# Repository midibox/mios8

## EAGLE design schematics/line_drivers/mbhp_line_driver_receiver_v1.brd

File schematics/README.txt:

Schematics can be viewed and edited with XCircuit
-> http://opencircuitdesign.com/xcircuit/

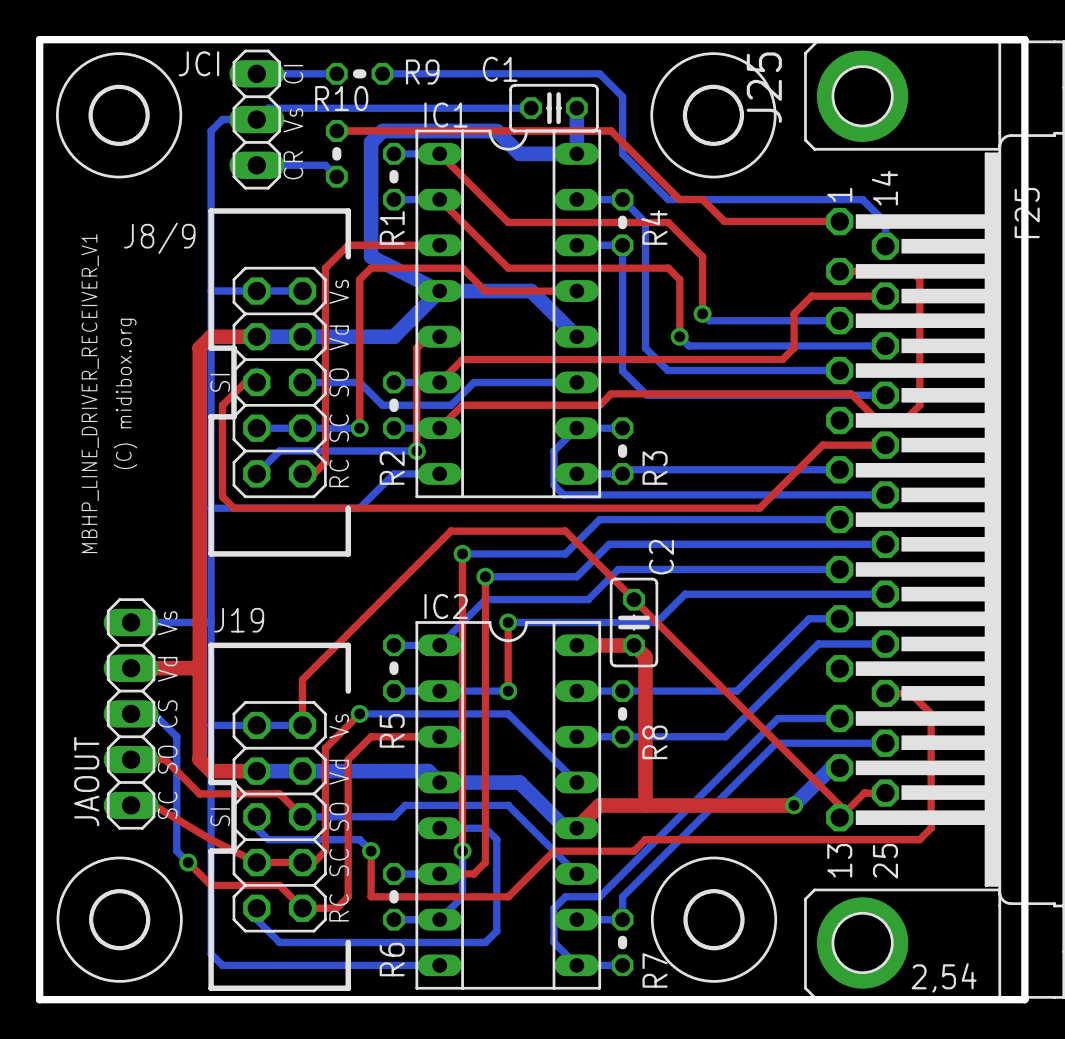
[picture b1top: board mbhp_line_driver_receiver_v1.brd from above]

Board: 2 copper layers, 54.7 x 53.3 mm, 23 parts (0 on the bottom side), 32 nets.

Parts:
C1, C2: 100n; C025-025X050
E$1, E$2, E$4, E$7: 3,0
IC1, IC2: MC3486; SOCKET-16
J8/9, J19: 2X05
J25: F25HP
JAOUT: 1X05
JCI: 1X03
R1, R2, R3, R4, R5, R6, R7, R8, R9, R10: 100; 0204V

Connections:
5V: C1.2, C2.2, IC1.4, IC1.12, IC1.16, IC2.4, IC2.12, IC2.16, J8/9.3, J8/9.4, J19.3, J19.4, J25.12, JAOUT.4
GND: C1.1, C2.1, IC1.8, IC2.8, J8/9.1, J8/9.2, J19.1, J19.2, J25.13, J25.25, JAOUT.5, JCI.2
S$1: IC2.11, J19.6, JAOUT.2
S$2: J19.5, J25.23
S$3: IC2.3, J19.10, JAOUT.3
S$4: IC2.13, J19.7, J19.8, JAOUT.1
S$5: IC2.5, J19.9
S$6: IC1.3, J8/9.10
S$7: IC1.5, J8/9.9
S$8: IC1.11, J8/9.6
S$9: IC1.13, J8/9.7, J8/9.8
S$10: IC1.15, J25.4, R4.1
S$11: IC1.14, J25.17, R4.2
S$12: IC1.10, J25.19, R3.1
S$13: IC1.9, J25.6, R3.2
S$14: IC2.15, J25.9, R8.1
S$15: IC2.14, J25.22, R8.2
S$16: IC2.10, J25.24, R7.1
S$17: IC2.9, J25.11, R7.2
S$18: IC2.2, J25.21, R5.2
S$19: IC2.1, J25.8, R5.1
S$21: IC2.6, J25.20, R6.1
S$22: IC2.7, J25.7, R6.2
S$24: IC1.7, J25.2, R2.2
S$25: IC1.6, J25.15, R2.1
S$26: IC1.2, J25.16, R1.2
S$27: IC1.1, J25.3, R1.1
S$28: JCI.1, R10.2
S$29: JCI.3, R9.2
S$30: J25.14, R9.1
S$31: J25.1, R10.1
SI1: J8/9.5, J25.18

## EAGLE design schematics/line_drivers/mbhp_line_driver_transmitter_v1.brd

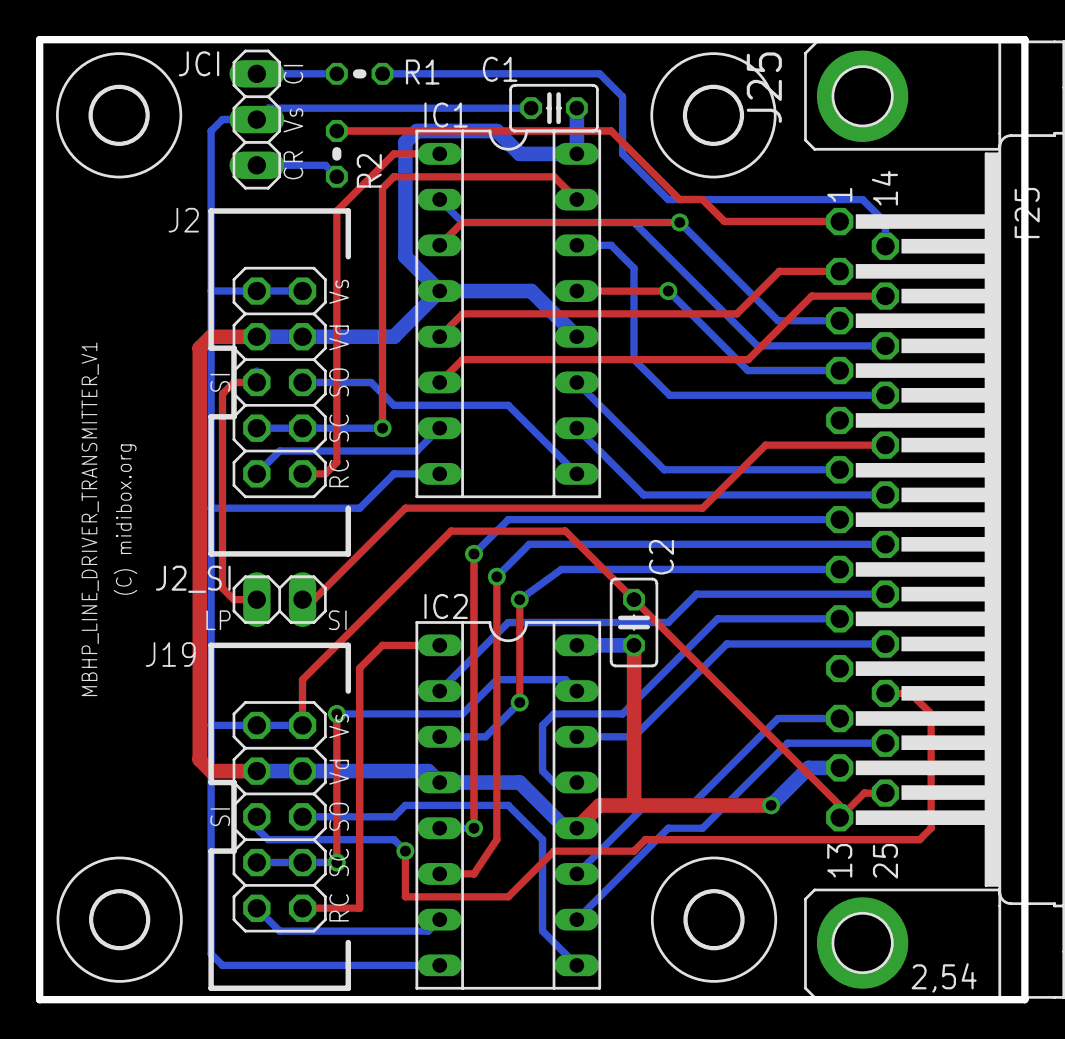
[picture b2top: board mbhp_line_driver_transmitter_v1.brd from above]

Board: 2 copper layers, 54.7 x 53.3 mm, 15 parts (0 on the bottom side), 33 nets.

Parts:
C1, C2: 100n; C025-025X050
E$1, E$2, E$4, E$7: 3,0
IC1, IC2: MC3487; SOCKET-16
J2, J19: 2X05
J2_SI: 1X02
J25: F25HP
JCI: 1X03
R1, R2: 100; 0204V

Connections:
5V: C1.2, C2.2, IC1.4, IC1.12, IC1.16, IC2.4, IC2.12, IC2.16, J2.3, J2.4, J19.3, J19.4, J25.12
GND: C1.1, C2.1, IC1.8, IC2.8, J2.1, J2.2, J19.1, J19.2, J25.13, J25.25, JCI.2
S$1: IC2.10, J25.24
S$2: J19.5, J25.23
S$3: IC2.9, J19.6
S$4: IC2.15, J19.7, J19.8
S$5: IC2.1, J19.10
S$6: IC2.7, J19.9
S$7: IC1.7, J2.9
S$8: IC1.1, J2.10
S$9: IC1.15, J2.7, J2.8
S$10: IC1.9, J2.6
S$11: IC2.11, J25.11
S$12: IC2.14, J25.22
S$13: IC2.13, J25.9
S$14: IC2.2, J25.21
S$15: IC2.3, J25.8
S$16: IC2.6, J25.20
S$17: IC2.5, J25.7
S$18: IC1.10, J25.19
S$19: IC1.11, J25.6
S$21: IC1.14, J25.17
S$22: IC1.13, J25.4
S$23: J2_SI.2, J25.18
S$24: IC1.2, J25.16
S$25: IC1.3, J25.3
S$26: IC1.6, J25.15
S$27: IC1.5, J25.2
S$28: JCI.1, R2.2
S$29: JCI.3, R1.2
S$30: J25.14, R1.1
S$31: J25.1, R2.1
SI1: J2.5, J2_SI.1

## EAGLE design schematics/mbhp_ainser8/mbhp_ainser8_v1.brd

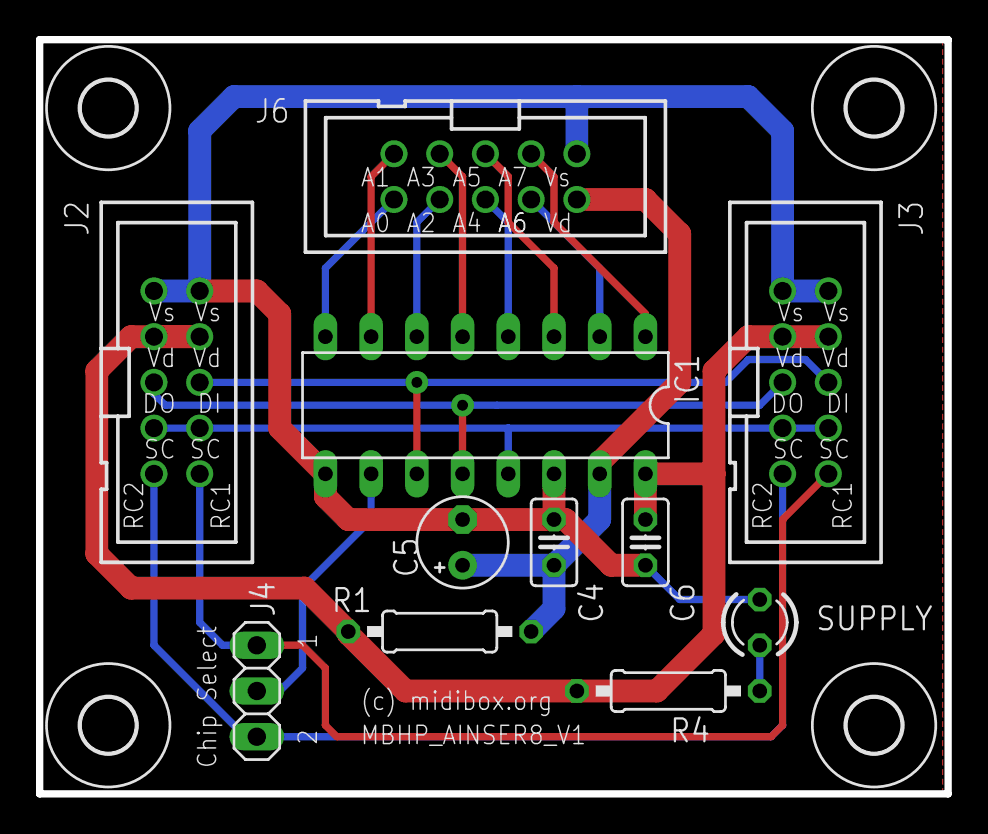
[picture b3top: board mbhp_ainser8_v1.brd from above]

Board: 2 copper layers, 50.5 x 41.9 mm, 15 parts (0 on the bottom side), 18 nets.

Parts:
C4, C6: 100nF; C025-025X050
C5: 10uF; E2,5-5
E$5, E$6, E$7, E$8: 3,0
IC1: MCP3208; DIL16
J2, J3, J6: PAK100/2500-10
J4: 1X03
R1: 10; 0207/10
R4: 470; 0207/10
SUPPLY: LED3MM

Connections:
CH0: IC1.1, J6.3
CH1: IC1.2, J6.4
CH3: IC1.4, J6.6
CH4: IC1.5, J6.7
CH5: IC1.6, J6.8
CH6: IC1.7, J6.9
CH7: IC1.8, J6.10
CS: IC1.10, J4.2
DI: IC1.11, J2.6, J3.6
DO: IC1.12, J2.5, J3.5
GND: C4.1, C5.-, C6.2, IC1.9, IC1.14, J2.1, J2.2, J3.1, J3.2, J6.1, SUPPLY.K
RC1: J2.10, J3.10, J4.1
RC2: J2.9, J3.9, J4.3
S$3: IC1.3, J6.5
S$73: R4.1, SUPPLY.A
SC: IC1.13, J2.7, J2.8, J3.7, J3.8
VCA: C4.2, C5.+, IC1.15, J6.2, R1.1
VCC: C6.1, IC1.16, J2.3, J2.4, J3.3, J3.4, R1.2, R4.2

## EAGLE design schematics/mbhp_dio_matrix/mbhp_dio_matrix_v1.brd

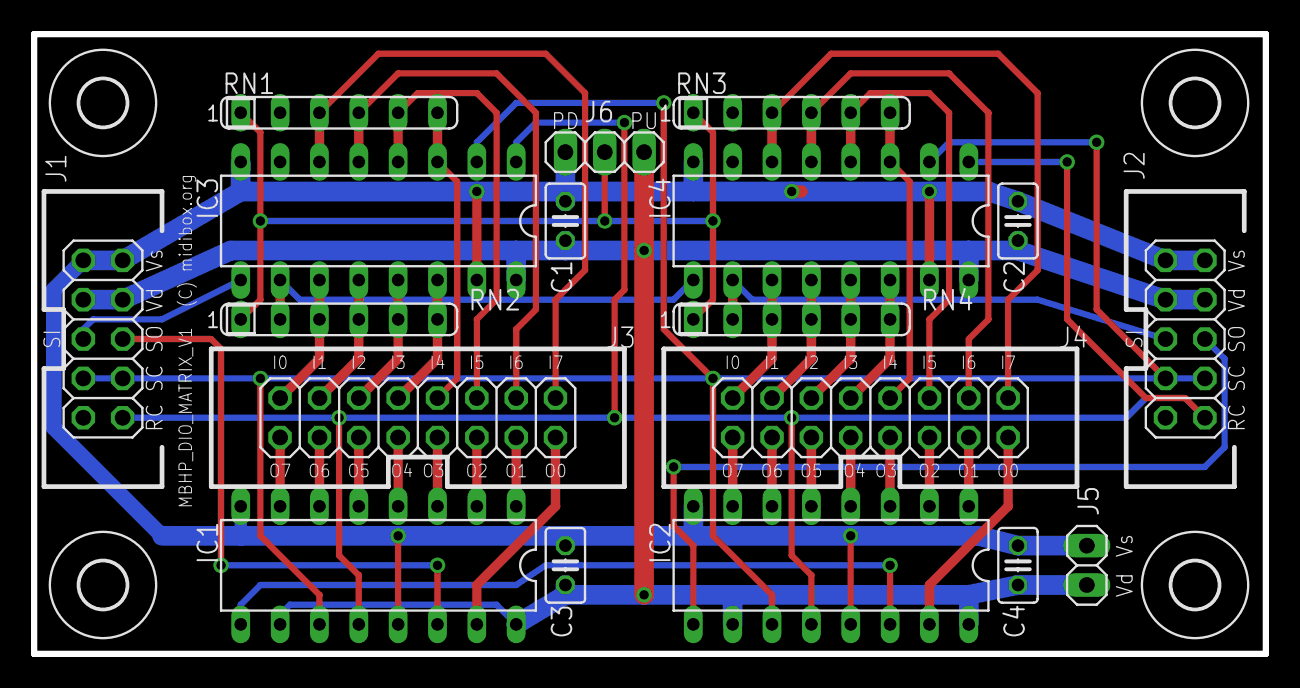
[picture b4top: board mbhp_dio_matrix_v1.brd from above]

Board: 2 copper layers, 79.5 x 40.0 mm, 22 parts (0 on the bottom side), 43 nets.

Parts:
C1, C2, C3, C4: 100nF; C025-025X050
E$1, E$2, E$3, E$4: 3,0
IC1, IC2: 74HC595; DIL16
IC3, IC4: 74HC165; DIL16
J1, J2: 2X05
J3, J4: 2X08
J5: 1X02
J6: 1X03
RN1, RN2, RN3, RN4: 5x10k; SIL6

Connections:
GND: C1.2, C2.2, C3.2, C4.2, IC1.8, IC1.13, IC2.8, IC2.13, IC3.8, IC3.15, IC4.8, IC4.15, J1.1, J1.2, J2.1, J2.2, J5.2, J6.3
RC: IC1.12, IC2.12, IC3.1, IC4.1, J1.10, J2.10
S$1: J6.2, RN1.1, RN2.1, RN3.1, RN4.1
S$2: IC1.9, IC2.14
S$3: IC3.11, J3.2, RN2.3
S$4: IC3.12, J3.4, RN2.4
S$5: IC3.13, J3.6, RN2.5
S$6: IC3.14, J3.8, RN2.6
S$7: IC3.3, J3.10, RN1.6
S$8: IC3.4, J3.12, RN1.5
S$9: IC3.5, J3.14, RN1.4
S$10: IC3.6, J3.16, RN1.3
S$11: IC4.11, J4.2, RN4.3
S$12: IC4.12, J4.4, RN4.4
S$13: IC4.13, J4.6, RN4.5
S$14: IC4.14, J4.8, RN4.6
S$15: IC4.3, J4.10, RN3.6
S$16: IC4.4, J4.12, RN3.5
S$17: IC4.5, J4.14, RN3.4
S$18: IC4.6, J4.16, RN3.3
S$19: IC3.10, IC4.9, RN2.2
S$20: IC4.10, J2.5, RN4.2
S$24: IC1.7, J3.1
S$25: IC1.6, J3.3
S$26: IC1.5, J3.5
S$27: IC1.4, J3.7
S$28: IC1.3, J3.9
S$29: IC1.2, J3.11
S$30: IC1.1, J3.13
S$31: IC1.15, J3.15
S$32: IC2.7, J4.1
S$33: IC2.6, J4.3
S$34: IC2.5, J4.5
S$35: IC2.4, J4.7
S$36: IC2.3, J4.9
S$37: IC2.2, J4.11
S$38: IC2.1, J4.13
S$39: IC2.15, J4.15
S$42: IC2.9, J2.6
SC: IC1.11, IC2.11, IC3.2, IC4.2, J1.7, J1.8, J2.7, J2.8
SI: IC3.9, J1.5
SO: IC1.14, J1.6
VDD: C1.1, C2.1, C3.1, C4.1, IC1.10, IC1.16, IC2.10, IC2.16, IC3.16, IC4.16, J1.3, J1.4, J2.3, J2.4, J5.1, J6.1

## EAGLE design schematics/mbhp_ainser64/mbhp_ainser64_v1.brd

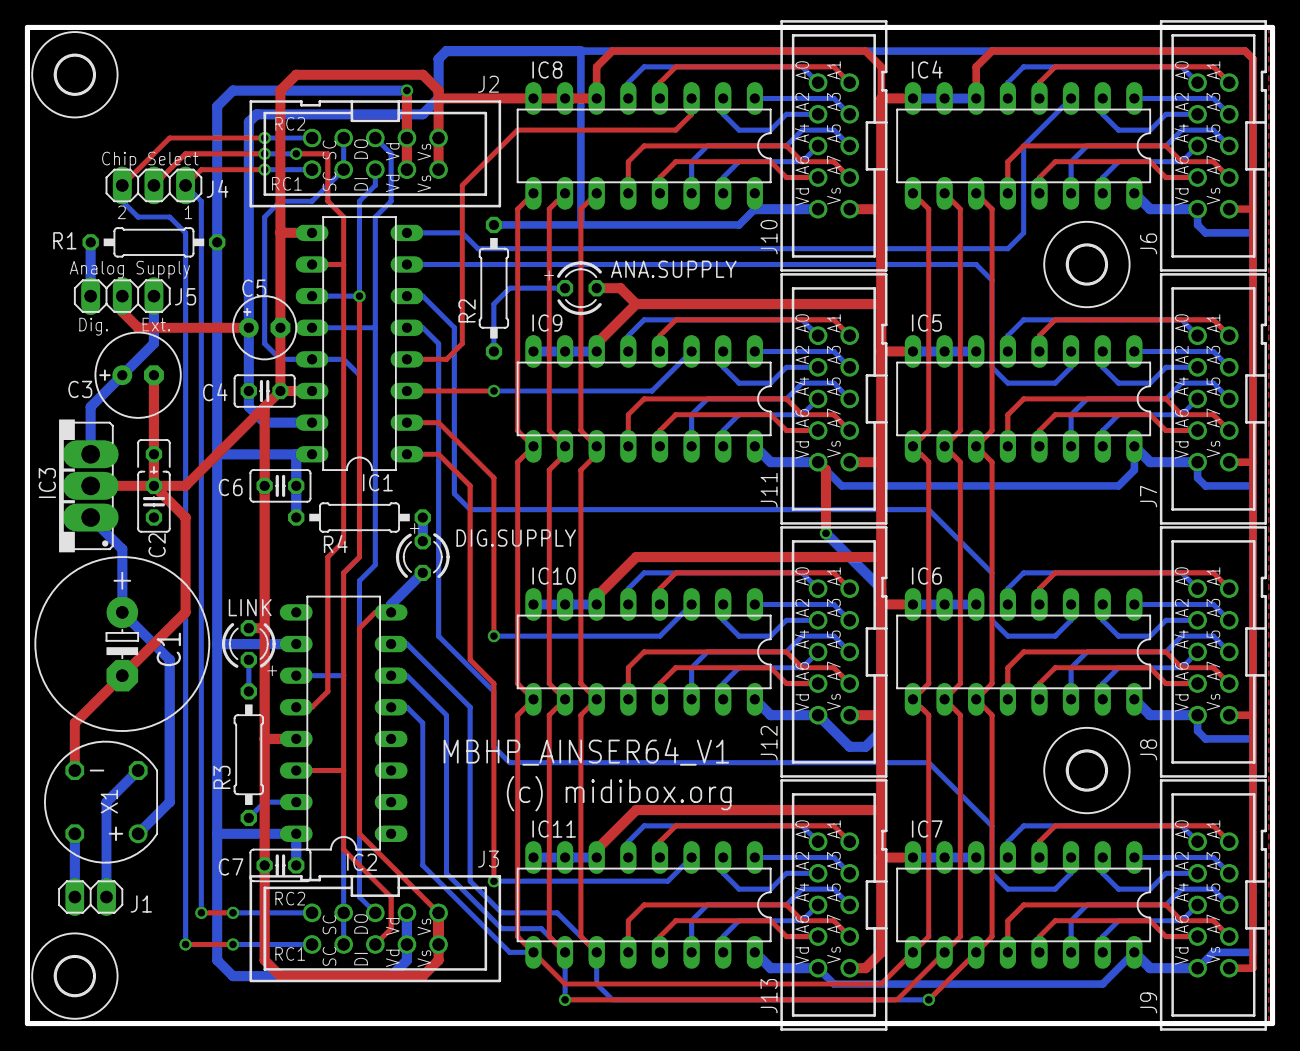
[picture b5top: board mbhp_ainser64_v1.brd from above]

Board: 2 copper layers, 100.0 x 80.0 mm, 43 parts (0 on the bottom side), 93 nets.

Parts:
ANA.SUPPLY: LED3MM
C1: 470uF; E5-13
C2: 330nF; C025_050-025X075
C3: 47uF; E2,5-7
C4, C6, C7: 100nF; C025-025X050
C5: 10uF; E2,5-5
DIG.SUPPLY: LED3MM
E$5, E$6, E$7, E$8: 3,0
IC1: MCP3208; DIL16
IC2: 74HC595; DIL16
IC3: 7805; 78XXS_
IC4, IC5, IC6, IC7, IC8, IC9, IC10, IC11: 4051; DIL16
J1: 1X02
J2, J3, J6, J7, J8, J9, J10, J11, J12, J13: PAK100/2500-10
J4, J5: 1X03
LINK: LED3MM
R1: 10; 0207/10
R2, R3, R4: 470; 0207/10
X1: B40C800; RB1A

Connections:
CH0: IC1.1, IC11.3
CH1: IC1.2, IC10.3
CH2: IC1.3, IC9.3
CH3: IC1.4, IC8.3
CH4: IC1.5, IC7.3
CH5: IC1.6, IC6.3
CH6: IC1.7, IC5.3
CH7: IC1.8, IC4.3
CS: IC1.10, IC2.12, J4.2
DI: IC1.11, IC2.14, J2.6, J3.6
DO: IC1.12, J2.5, J3.5
GND: ANA.SUPPLY.K, C1.-, C2.2, C2.3, C3.-, C4.1, C5.-, C6.2, C7.2, DIG.SUPPLY.K, IC1.9, IC1.14, IC2.8, IC2.13, IC3.GND, IC4.6, IC4.7, IC4.8, IC5.6, IC5.7, IC5.8, IC6.6, IC6.7, IC6.8, IC7.6, IC7.7, IC7.8, IC8.6, IC8.7, IC8.8, IC9.6, IC9.7, IC9.8, IC10.6, IC10.7, IC10.8, IC11.6, IC11.7, IC11.8, J2.1, J2.2, J3.1, J3.2, J6.1, J7.1, J8.1, J9.1, J10.1, J11.1, J12.1, J13.1, LINK.K, X1.-
MUXA: IC2.5, IC4.9, IC5.9, IC6.9, IC7.9, IC8.9, IC9.9, IC10.9, IC11.9
MUXB: IC2.6, IC4.10, IC5.10, IC6.10, IC7.10, IC8.10, IC9.10, IC10.10, IC11.10
MUXC: IC2.7, IC4.11, IC5.11, IC6.11, IC7.11, IC8.11, IC9.11, IC10.11, IC11.11
RC1: J2.9, J3.10, J4.3
RC2: J2.10, J3.9, J4.1
S$1: IC4.5, J6.10
S$2: IC4.4, J6.9
S$3: IC4.2, J6.8
S$4: IC4.1, J6.7
S$5: IC4.15, J6.6
S$6: IC4.14, J6.5
S$7: IC4.13, J6.4
S$8: IC4.12, J6.3
S$9: J1.2, X1.AC1
S$11: IC5.5, J7.10
S$12: IC5.4, J7.9
S$13: IC5.2, J7.8
S$14: IC5.1, J7.7
S$15: IC5.15, J7.6
S$16: IC5.14, J7.5
S$17: IC5.13, J7.4
S$18: J1.1, X1.AC2
S$19: IC5.12, J7.3
S$21: IC6.5, J8.10
S$22: IC6.4, J8.9
S$23: IC6.2, J8.8
S$24: IC6.1, J8.7
S$25: IC6.15, J8.6
S$26: IC6.14, J8.5
S$27: C3.+, IC3.OUT, J5.1
S$28: IC6.13, J8.4
S$29: IC6.12, J8.3
S$31: IC7.5, J9.10
S$32: IC7.4, J9.9
S$33: IC7.2, J9.8
S$34: IC7.1, J9.7
S$35: IC7.15, J9.6
S$36: C1.+, IC3.IN, X1.+
S$37: IC7.14, J9.5
S$38: IC7.13, J9.4
S$39: IC7.12, J9.3
S$41: IC8.5, J10.10
S$42: IC8.4, J10.9
S$43: IC8.2, J10.8
S$44: IC8.1, J10.7
S$45: IC2.15, R3.1
S$46: IC8.15, J10.6
S$47: IC8.14, J10.5
S$48: IC8.13, J10.4
S$49: IC8.12, J10.3
S$51: IC9.5, J11.10
S$52: IC9.4, J11.9
S$53: IC9.2, J11.8
S$54: J5.3, R1.1
S$55: IC9.1, J11.7
S$56: IC9.15, J11.6
S$57: IC9.14, J11.5
S$58: IC9.13, J11.4
S$59: IC9.12, J11.3
S$61: IC10.5, J12.10
S$62: IC10.4, J12.9
S$63: LINK.A, R3.2
S$64: IC10.2, J12.8
S$65: IC10.1, J12.7
S$66: IC10.15, J12.6
S$67: IC10.14, J12.5
S$68: IC10.13, J12.4
S$69: IC10.12, J12.3
S$71: IC11.5, J13.10
S$72: ANA.SUPPLY.A, R2.1
S$73: DIG.SUPPLY.A, R4.1
S$74: IC11.4, J13.9
S$75: IC11.2, J13.8
S$76: IC11.1, J13.7
S$77: IC11.15, J13.6
S$79: IC11.14, J13.5
S$80: IC11.13, J13.4
S$81: IC11.12, J13.3
SC: IC1.13, IC2.11, J2.7, J2.8, J3.7, J3.8
VCA: C4.2, C5.+, IC1.15, IC4.16, IC5.16, IC6.16, IC7.16, IC8.16, IC9.16, IC10.16, IC11.16, J5.2, J6.2, J7.2, J8.2, J9.2, J10.2, J11.2, J12.2, J13.2, R2.2
VCC: C6.1, C7.1, IC1.16, IC2.10, IC2.16, J2.3, J2.4, J3.3, J3.4, R1.2, R4.2

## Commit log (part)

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2019-03-02 various updates for MBSEQ manual
2019-03-02 mios_enc modes: added hint about originator
2019-03-02 MBFM: changed version number which is displayed on LCD
2019-03-02 midibox_fm_v1_1d
2019-03-02 USB_MIDI_PIC: fixed comments
2019-03-02 mios_enc: corrected mapping
2019-03-02 - Fixed TextPane resizing
2019-03-02 mios_v1_9g
2019-03-02 minor change in MIOS V1.9g changelog
2019-03-02 added MBHP_BLM_SCALAR
2019-03-02 try: new encoder mode decoding as proposed by avogra
2019-03-02 MBHP_USB_PIC: fixed SysEx issue under MacOS
2019-03-02 midibox_sid_v2_0rc33
2019-03-02 MBSEQ doc update
2019-03-02 MIOS Studio: loading large hex files into upload window now significantly faster
2019-03-02 - Added MRU Lists for SysexSendReceiveGUI - Added XML save/restore for SysexSendReceive
2019-03-02 midibox_seq_v3_4f, midibox_808_v1_1a
2019-03-02 MIOS Studio: send/edit SysEx streams
2019-03-02 - Added fix for resizing windows
2019-03-02 improved MBSEQ and MBHP page
2019-03-02 MB64E and MBCV: added comment about re-release to changelog
2019-03-02 MBHP_USB_PIC: swapped Rx/Tx LED
2019-03-02 MBSID: fixed race condition in SusKey portamento handler
2019-03-02 MIOS Studio: added Receive function to SysEx window
2019-03-02 MBSID: implemented "All Notes Off" (CC#123)
2019-03-02 mios_enc: fixed last typo?
2019-03-02 mios_enc: changed code again (now I know what went wrong;)
2019-03-02 MBSEQ manual updates
2019-03-02 mios_enc: fixed another typo
2019-03-02 MBSID: added TODO
2019-03-02 MBSID: more sammichSID changes provided by Wilba
2019-03-02 some website updates
2019-03-02 MB64: added meta example
2019-03-02 BLM_SCALAR: compatibility update
2019-03-02 MBAY V1 RC1 Bankstick implementation (For Patches)
2019-03-02 initial version of BLM_SCALAR firmware
2019-03-02 midibox64_v2_4d, midibox64e_v2_2d
2019-03-02 ucapps: added description for ultra low cost SD card adapter
2019-03-02 - Added better support for OSX, still incomplete
2019-03-02 mbfm_interconnection_test_v1d
2019-03-02 ... more Windows MDI fixes
2019-03-02 ... more Windows fixes
2019-03-02 fixd the buttons hickups
2019-03-02 Fixed bug in CS_MENU_MATRIX_SammichSID_Column_Remap
2019-03-02 MBSID: added direct WT position control via key number
2019-03-02 reverted to working rev 860 *cough*
2019-03-02 MBSID interconnection test: fixed obligatory typo
2019-03-02 MB808: GP LEDs show track activity in mute page
2019-03-02 ...try again
2019-03-02 preparing MIOSStudio 9.4
2019-03-02 - fix for Windows MDI
2019-03-02 overworked interconnection tests
2019-03-02 ucapps: updated MIDI troubleshooting page
2019-03-02 the initial commit
2019-03-02 MB64E: added setup w/o LED rings
2019-03-02 correction for encoders
2019-03-02 ...and added some comments
2019-03-02 updated MBHP_ETH module
2019-03-02 midibox_sid_v2_0_rc35
2019-03-02 ucapps: described MIDI slider issue
2019-03-02 ucapps mbseq: new manual page
2019-03-02 protodeck features added to the README.txt
2019-03-02 BLM_SCALAR: final version
2019-03-02 protodeck: removed expired Makefile.orig
2019-03-02 cleaned up protodeck source directories
2019-03-02 MBSID: fixed modmatrix artifacts
2019-03-02 the last move (sorry)
2019-03-02 moving the protodeck's other folders (oops!!)
2019-03-02 midibox_sid_v2_0_rc37
2019-03-02 BLM_SCALAR: improved timeout mechanism
2019-03-02 BLM_SCALAR: added rotated view
2019-03-02 LCD handling
2019-03-02 ucapps updates
2019-03-02 midibox_sid_v2_0_rc36
2019-03-02 website changes for MIOS Studio 2
2019-03-02 updated MBHP_BLM_SCALAR schematics
2019-03-02 BLM schematic: added expired to interconnection diagram
2019-03-02 BLM scalar: backup of current code (not completed yet...)
2019-03-02 MBSID: support for extended patch format
2019-03-02 ucapps: some website updates
2019-03-02 added routing example
2019-03-02 added mbhp_mf_v3 application
2019-03-02 added blm_connector
2019-03-02 MBFM: bugfix for finetune
2019-03-02 MIOS Studio updates
2019-03-02 mbhp_mf_v2 and v3 schematics
2019-03-02 mbhp_eth schematic: another alignment to seppomans variant
2019-03-02 routing variant: change split point
2019-03-02 changed LFO page menu order for sammichFM
2019-03-02 MBHP_MF firmware
2019-03-02 routing variants: add comment
2019-03-02 MIOS: set BSR when calling MIOS_MF_Enable
2019-03-02 ucapps updated
2019-03-02 MBFM: fixed makefile for PIC18F452 derivatives (memory image too large for 32k devices)
2019-03-02 MBLC: USER_Timer was clocked too fast
2019-03-02 MBSID: added bug report from Wilba
2019-03-02 some ucapps updates
2019-03-02 repaired asm_skeleton
2019-03-02 MBFM: bugfix for EXEC_TOGPAR
2019-03-02 MBHP_ETH schematic: aligned C numbers with seppomans PCB
2019-03-02 mbhp_usb_pic18f2550: fixed C3
2019-03-02 routing variants: make MIDI channel mapping clear
2019-03-02 added MBHP_MF_V3 to the SYSEX_HEADERS doc
2019-03-02 MBFM: fixed INS display bug in AOUT page
2019-03-02 overworked mbseq_v4_interconnection schematic
2019-03-02 asm_skeleton accident
2019-03-02 Added support for controlling OPL3 with PIC18F4685
2019-03-02 mbfm: it wasn't possible to store a patch anymore
2019-03-02 midibox_fm_v1_2a
2019-03-02 MBFM: updated README
2019-03-02 midibox_fm_v1_4
2019-03-02 MBFM: improved modulation assignments again
2019-03-02 MBFM: some code cleanup
2019-03-02 midibox_fm_v1_2
2019-03-02 MBFM: ...and added simplifcation
2019-03-02 BLM_SCALAR: removed references to old BLM driver
2019-03-02 midibox_fm_v1_3
2019-03-02 MBFM: bugfix for modulation depth/init changes
2019-03-02 added blm_scalar_4x8x8_buttons
2019-03-02 MBSID: added new request to wishlist
2019-03-02 midibox_808_v1_1c
2019-03-02 MBHP_USB_GM5 eeprom: moved blocker to 0x7200
2019-03-02 mbhp_mf_v3: update for MBLC V2 interaction
2019-03-02 MBFM: added non-destructive CC assignment changes
2019-03-02 midio128_v3_scanmatrix.ps corrected (copy&paste error)
2019-03-02 MIDI force to scale v1.0
2019-03-02 MBSEQ: bugfix for legato
2019-03-02 ucapps: first updates for LPC17
2019-03-02 mbhp_core_lpc17.ps: CAN R8 -> R11
2019-03-02 mb808: display re-init when instrument encoder is moved (for mute page)
2019-03-02 MB808: added wishlist
2019-03-02 ucapps schematic updates
2019-03-02 updated mbfm_interconnection test for MBFM
2019-03-02 midibox_sid_v2_0_rc38
2019-03-02 midibox_fm_v1_4c
2019-03-02 mbhp_core_lpc17: different 74HC type depending on LCD voltage option
2019-03-02 MBSID V2: allow to pass filter mode/channel and waveform flags to J5
2019-03-02 MIOS SysEx implementation doc: added error code 0xb and 0xc
2019-03-02 MBSEQ V3: try for legato gates
2019-03-02 mbhp_iic_speakjet: fixed baudrate init
2019-03-02 mbfm_mf_v3_0
2019-03-02 MBSID V2: MBNet optimisations for remote access
2019-03-02 mbhp_lcd_ssd1306 schematics
2019-03-02 MBFM: changed way how drums are triggered
2019-03-02 MBSEQ V3: added changelog entry
2019-03-02 midibox_808_v1_2pre1
2019-03-02 first version of MBHP_CORE_LPC17 module
2019-03-02 MBSEQ: another legato fix
2019-03-02 added mbseq_lite_blm
2019-03-02 midibox_fm_v1_4a
2019-03-02 midi_force_to_scale_v1_1
2019-03-02 mbhp_core_lpc17.ps: fixed typo
2019-03-02 demo app for simple controllers
2019-03-02 MBHP_MF_NG: enhanced number of CCs
2019-03-02 First commit of mbvm
2019-03-02 MBKB schematics
2019-03-02 mbhp_dio_matrix: another minor improvement
2019-03-02 MBFM: SD experiment
2019-03-02 midibox_seq_v4_050
2019-03-02 some doc updates
2019-03-02 MBHP_AINSER64: layout updates
2019-03-02 mbhp_dio_matrix.brd: modified as requested by Olimex
2019-03-02 MBSID: improved LFO MIDI clock sync
2019-03-02 mbhp_dio_matrix: some minor improvements
2019-03-02 MBSIDV2 TODO update
2019-03-02 MBHP_AINSER64 schematic + layout
2019-03-02 added mbhp_dio_matrix
2019-03-02 MBHP_MF_V3 -> NG
2019-03-02 midibox_sid_v2_040
2019-03-02 renamed MBHP_MF_V3->NG
2019-03-02 updated visual metronome
2019-03-02 MBCV/SID/FM: handle song position like midi start
2019-03-02 added schematic for DOGM128
2019-03-02 midibox_sid_v2_039
2019-03-02 mbhp_dio_matrix.brd finalized
2019-03-02 visual metronome: added README.txt
2019-03-02 midibox_sid_v2_041
2019-03-02 srio_interconnection_test
2019-03-02 MBSEQDR: global accent also for MIDI/AOUT
2019-03-02 mbhp_mf_ng_v1_003
2019-03-02 MB64E: faster bank load, improved snapshot at poweron
2019-03-02 midibox64e_sfb_table.txt: fixed typo
2019-03-02 MB64 v2.4f
2019-03-02 midibox_808_v1_3a
2019-03-02 midibox_fm_v1_4e
2019-03-02 midibox_808_v1_3
2019-03-02 MBSEQDR: some progress
2019-03-02 midibox64_v2_4e
2019-03-02 MB808: added setup for MBSEQDR
2019-03-02 MBSEQDR: setup completed, tests successfull!
2019-03-02 some schematic updates
2019-03-02 MBKB: Fatar adapter updates
2019-03-02 MIDImerger for PIC16F88: corrected sample frequency
2019-03-02 midibox_sid_v2_042
2019-03-02 MB64E: last patch ;-)
2019-03-02 MBSID: minor doc typo corrected
2019-03-02 MBFM/MBSID: Ctrlr panel updates
2019-03-02 MBSID/MBFM: Ctrlr panels
2019-03-02 midibox_lc_v1_6f
2019-03-02 midibox_lc_v1_6g
2019-03-02 MBSID Ctrlr Panel: changed version number
2019-03-02 mbhp_ainser8
2019-03-02 MBSID/MBFM: renamed Ctrlr panels
2019-03-02 MB64E: add another meta example
2019-03-02 updated ucapps docs
2019-03-02 aout: fixed README.txt
2019-03-02 MB64: simplify datawheel config
2019-03-02 moved LED updates and metronome note definition to display Tick function. Removed redundant code from main.c
2019-03-02 MBHP_CORE_STM32F4 schematic
2019-03-02 Corrected LED behaviour on preset recall
2019-03-02 MBSID: fix envelope on PLAY button
2019-03-02 midibox_sid_v2_043
2019-03-02 MB64E: added meta event example for note events
2019-03-02 midibox_fm_v1_4g
2019-03-02 schematic updates
2019-03-02 corrected typo in mbhp_aout_mcp4822.ps
2019-03-02 MBFM: allow to change WT when they are stored in RAM
2019-03-02 MBHP_CORE_STM32F4 schematic update
2019-03-02 midibox_fm_v1_4h
2019-03-02 mbhp_aout_mcp
2019-03-02 Removing "sequencers"
2019-03-02 another schematic update
2019-03-02 MBSID: improve ENC behaviour
2019-03-02 added line driver schematic
2019-03-02 MBSID: added enc speed test
2019-03-02 midibox_fm_v1_4i
2019-03-02 MBFM: avoid compiler warning for PIC18F452
2019-03-02 MBFM: Ctrlr panel updates for latest version
2019-03-02 MB808: improved dimming for gate triggers
2019-03-02 MB808: new options
2019-03-02 mbhp_mf_ng_v1_005
2019-03-02 MBHP_MIDI_IO: fixed input supply voltage
2019-03-02 added schematics for line drivers
2019-03-02 MBFM: corrected doc
2019-03-02 adaptions to latest Ctrlr version
2019-03-02 mbhp_core_stm32f4 schematic: fixed typo
2019-03-02 MB808: improved Gate/Aux layer handling
2019-03-02 mbhp_mf_ng: added README.txt
2019-03-02 MBFM: support for 8bit LCDs
2019-03-02 added mbhp_midi_io schematic
2019-03-02 BLM scalar: another bugfix...
2019-03-02 ucapps update
2019-03-02 MBSID: added new presets
2019-03-02 BLM_SCALAR: allow to define the number of AINs
2019-03-02 BLM scalar: fixed pin assignment for BLM_AIN_PIN_MAP
2019-03-02 blm_scalar_v1_1
2019-03-02 MIDIO128: support for AIN
2019-03-02 BLM scalar: make ain_map unsigned char
2019-03-02 blm_scalar: corrected name
2019-03-02 fixed initialization bug (in-out map was not built on init)
2019-03-02 MBSID: improved MIDI clock sync + added new bassline patch
2019-03-02 BLM scalar: add optional mappings
2019-03-02 MIDIbox SID V2: added SuperSaw detune mode (created by Lis0r)
2019-03-02 MBSIDV2: added instrument selection via SysEx
2019-03-02 fixed braces and indentation
2019-03-29 updated svnmios -> github
2020-02-16 MB808: added setup_9090_stormb
2020-02-16 MB808 9090 setup: use global accent
2020-02-16 MB808: improved 9090 setup
2020-02-16 MB808 909 setup: enable switch
2020-05-27 MBSID C64 PSU: connect pin 4+5 together to comply with various PSU implementations
2020-07-24 Fix CLCD init sequence for WS0010/RS0010 displays
    Remove commands that appear to be an incomplete duplicate the of
    commands that immediately follow (display off, display clear).
    This fixes compatibility with modern OLED character displays based on
    the Winstar WS0010 or Raystar RS0010 controller.
    Tested with Raystar REC002004AYPP5N00000.
2023-10-26 MIDIbox_SID_V2.panel* updates
2023-10-26 added MIDIbox_SID_V2.bpanelz
2023-10-28 MB6582: swapping Inc/Dec button
